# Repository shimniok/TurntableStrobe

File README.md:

# TurntableStrobe

Check your turntable's speed with TurntableStrobe, a highly accurate, tiny, low-cost, handheld turntable strobe. Or retrofit your turntable with the permanent-mount version.

With a crystal rated ±0.003% accuracy at 25°C, it is far more accurate than a mains frequency strobe on most turntables.

For sale on [Tindie](https://www.tindie.com/products/bot_thoughts/pocket-turntable-strobe/)

[Documentation](https://github.com/shimniok/TurntableStrobe/tree/master/documentation/)

## Features

* Crystal rated at ±0.003% accuracy at 25°C
* Use these free strobe discs: 60HzStrobeDisc.pdf or 50HzStrobeDisc.pdf
* Tiny CR1225 battery, included
* 1" long (not including the LED) x 3/4" wide
* Tactile on switch
* Handheld or Permanent mount

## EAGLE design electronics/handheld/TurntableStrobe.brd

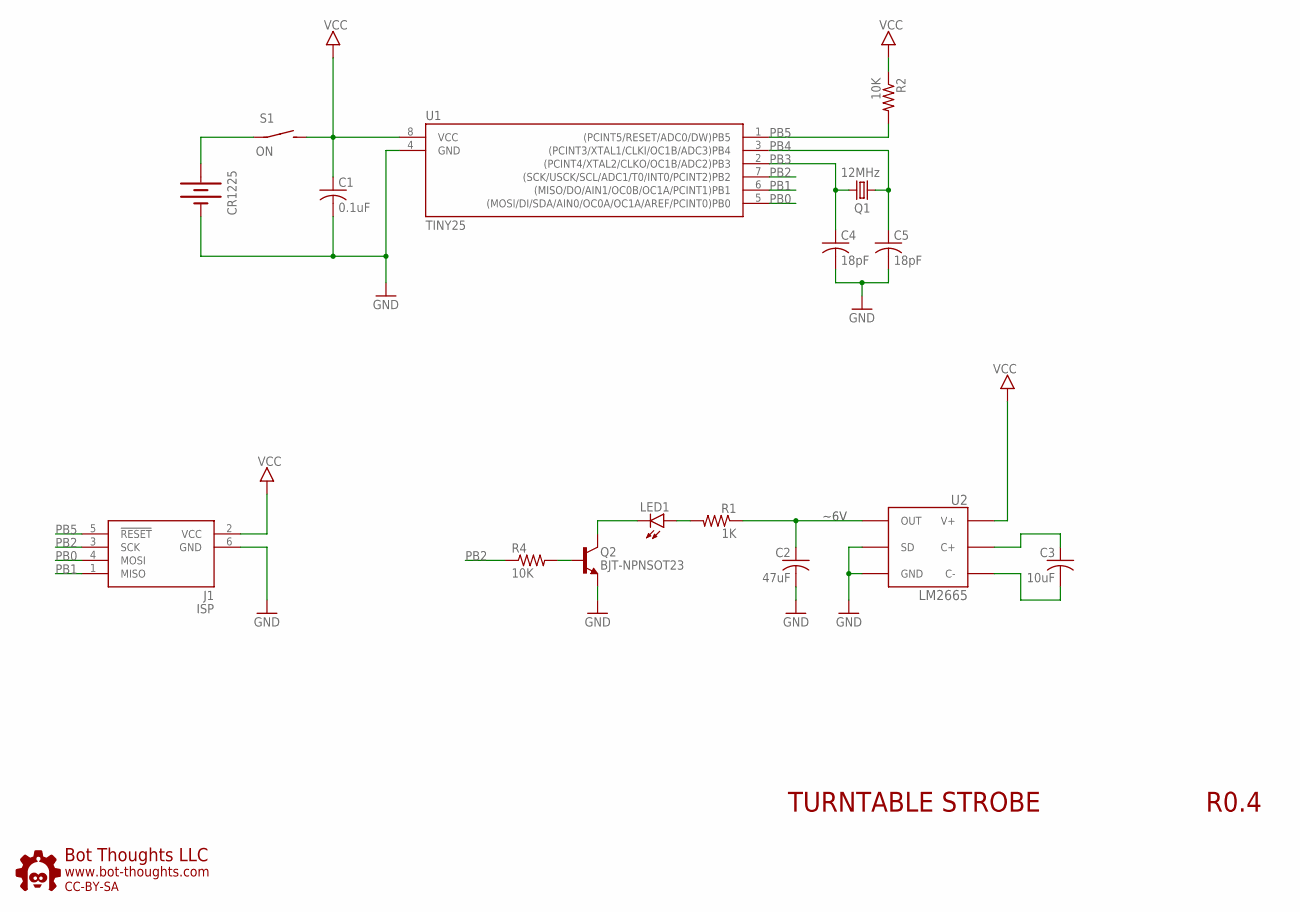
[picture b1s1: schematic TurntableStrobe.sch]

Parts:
C1: 0.1uF; C0603
C2: 47uF; C0603
C3: 10uF; C0603
C4, C5: 18pF; C0603
CR1225: BATTERY12PTH; BATTCON_12MM_PTH
J1: ISP; 2X3_TP
LED1: LED5MMRA
Q1: 12MHz; NDK_2PAD_5X3
Q2: BJT-NPNSOT23; SOT-23
R1: 1K; R0603
R2, R4: 10K; R0603
S1: ON; 6MMTACTILE_RECT
U1: TINY25; SOIC8N
U2: LM2665; SOT23-6
U$5: BTLOGO-LOGO-SM; BTLOGOS

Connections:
GND: C1.2, C2.2, C4.2, C5.2, CR1225.GND (-), J1.6 (GND), Q2.2 (E), U1.4 (GND), U2.2 (GND), U2.4 (SD)
unnamed: Q2.3 (B), R4.2
unnamed: C3.1, U2.6 (C+)
unnamed: LED1.A, R1.2
unnamed: C3.2, U2.3 (C-)
unnamed: LED1.C, Q2.1 (C)
PB0: J1.4 (MOSI), U1.5 ((MOSI/DI/SDA/AIN0/OC0A/OC1A/AREF/PCINT0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)
PB1: J1.1 (MISO), U1.6 ((MISO/DO/AIN1/OC0B/OC1A/PCINT1)PB1)
PB2: J1.3 (SCK), R4.1, U1.7 ((SCK/USCK/SCL/ADC1/T0/INT0/PCINT2)PB2)
PB3: C4.1, Q1.P$2 (2), U1.2 ((PCINT4/XTAL2/CLKO/OC1B/ADC2)PB3)
PB4: C5.1, Q1.P$1 (1), U1.3 ((PCINT3/XTAL1/CLKI/OC1B/ADC3)PB4)
PB5: J1.5 (!RESET), R2.2, U1.1 ((PCINT5/RESET/ADC0/DW)PB5)
VBAT: CR1225.VCC@1 (+), S1.P$1
VCC: C1.1, J1.2 (VCC), R2.1, S1.P$2 (S), U1.8 (VCC), U2.1 (V+)
VHI: C2.1, R1.1, U2.5 (OUT)

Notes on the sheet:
~6V
TURNTABLE STROBE
R0.4

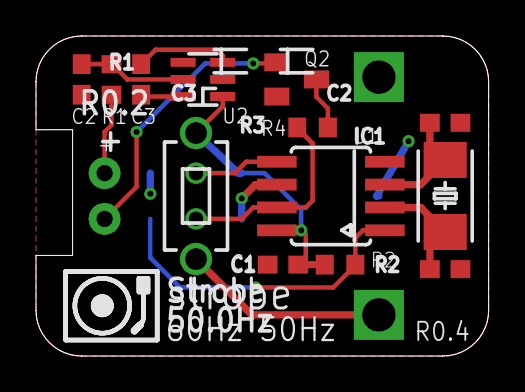
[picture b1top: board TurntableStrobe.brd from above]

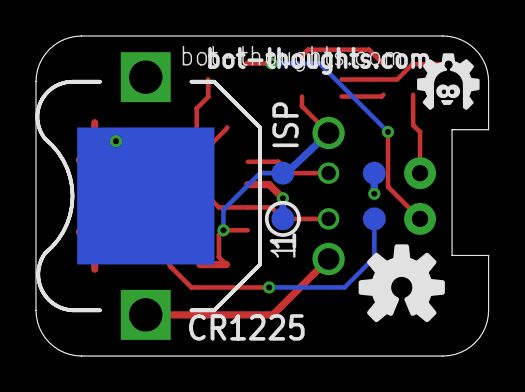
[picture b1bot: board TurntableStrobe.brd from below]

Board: 2 copper layers, 25.1 x 17.8 mm, 17 parts (3 on the bottom side), 15 nets.

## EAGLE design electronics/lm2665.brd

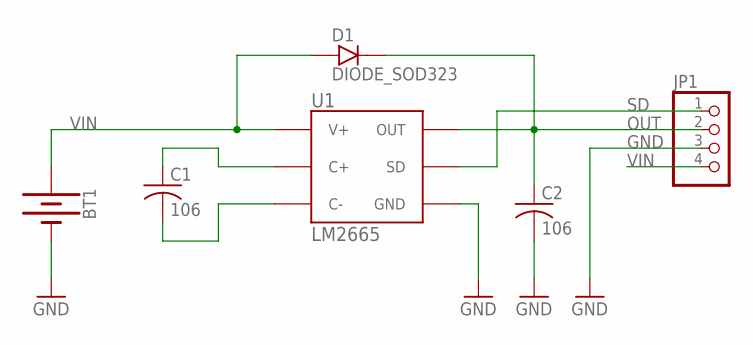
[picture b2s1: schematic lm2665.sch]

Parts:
BT1: BATTERY-12MM_PTH; BATTCON_12MM_PTH
C1, C2: 106; 1206
D1: DIODE_SOD323; SOD-323
JP1: PINHD-1X04_2.54-S; 1X04-S
U1: LM2665; SOT23-6

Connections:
GND: BT1.GND (-), C2.2 (-), JP1.3, U1.2 (GND)
unnamed: C1.1 (+), U1.6 (C+)
unnamed: C1.2 (-), U1.3 (C-)
OUT: C2.1 (+), D1.C, JP1.2, U1.5 (OUT)
SD: JP1.1, U1.4 (SD)
VIN: BT1.VCC@1 (+), D1.A, JP1.4, U1.1 (V+)

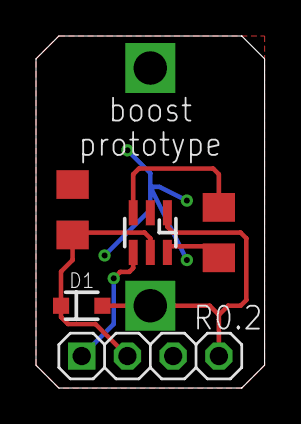
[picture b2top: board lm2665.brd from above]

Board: 2 copper layers, 12.7 x 19.6 mm, 6 parts (1 on the bottom side), 6 nets.

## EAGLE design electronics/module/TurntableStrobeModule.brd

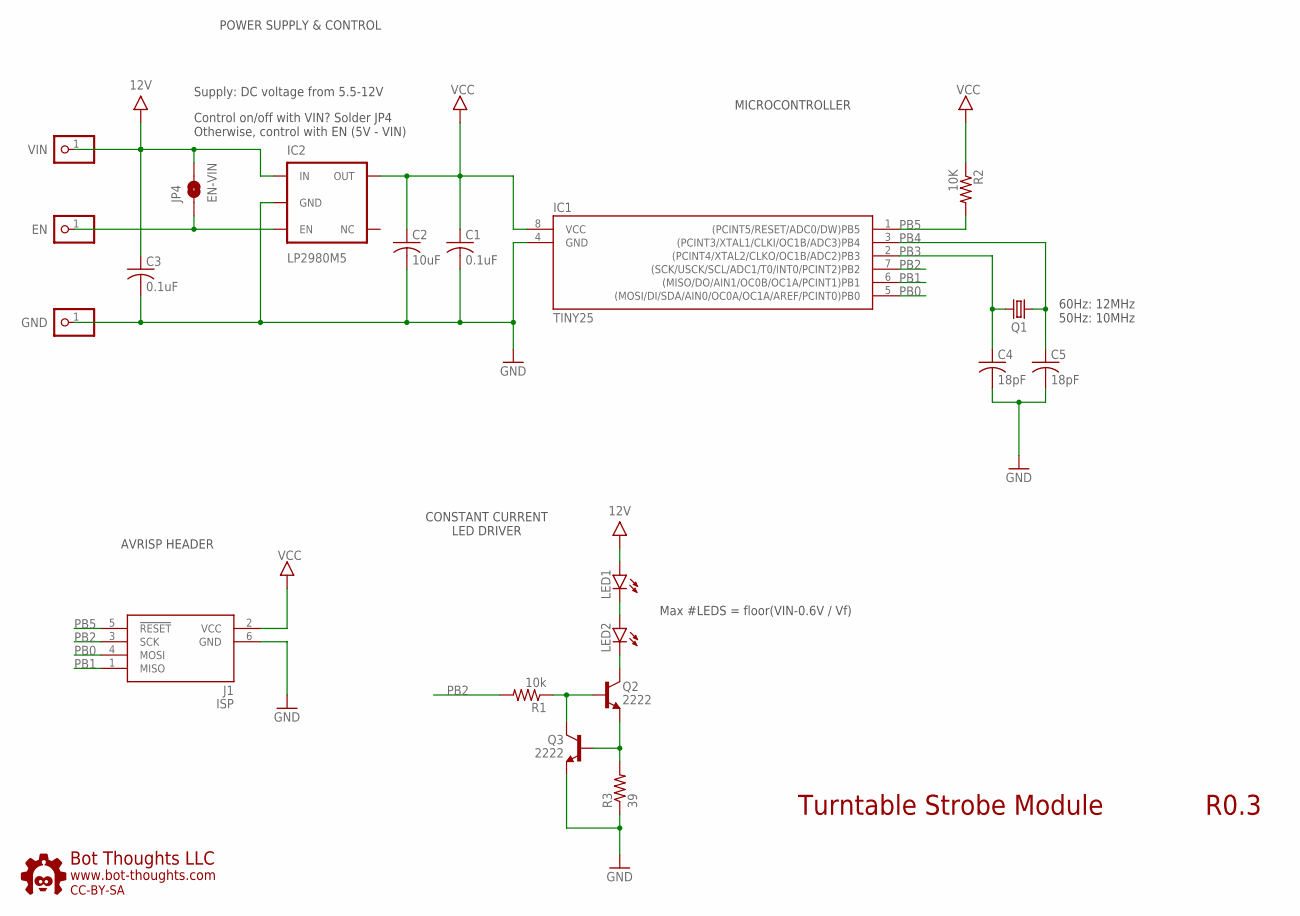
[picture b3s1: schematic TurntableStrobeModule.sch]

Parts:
C1, C3: 0.1uF; 0603
C2: 10uF; 1206
C4, C5: 18pF; 0603
IC1: TINY25; SOIC8N
IC2: LP2980M5; SOT23-5
J1: ISP; CON6P2R
JP1: EN; 1X01-S
JP2: VIN; 1X01-S
JP3: GND; 1X01-S
JP4: EN-VIN; SMT-JUMPER_2_NO_SILK
LED1, LED2: LED5MMRA
Q1: CRYSTALNDK5X3; NDK_2PAD_5X3
Q2, Q3: 2222; SOT-23
R1: 10k; 0603
R2: 10K; 0603
R3: 39; 0603
U$6: BTLOGO-LOGO-MD; BTLOGOM

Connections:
9V: C3.1 (+), IC2.1 (IN), JP2.1, JP4.2, LED1.A
GND: C1.2 (-), C2.2 (-), C3.2 (-), C4.2 (-), C5.2 (-), IC1.4 (GND), IC2.2 (GND), J1.6 (GND), JP3.1, Q3.2 (E), R3.1
unnamed: Q2.3 (B), Q3.1 (C), R1.1
unnamed: LED1.C, LED2.A
unnamed: LED2.C, Q2.1 (C)
unnamed: Q2.2 (E), Q3.3 (B), R3.2
unnamed: IC2.3 (EN), JP1.1, JP4.1
PB0: IC1.5 ((MOSI/DI/SDA/AIN0/OC0A/OC1A/AREF/PCINT0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), J1.4 (MOSI)
PB1: IC1.6 ((MISO/DO/AIN1/OC0B/OC1A/PCINT1)PB1), J1.1 (MISO)
PB2: IC1.7 ((SCK/USCK/SCL/ADC1/T0/INT0/PCINT2)PB2), J1.3 (SCK), R1.2
PB3: C4.1 (+), IC1.2 ((PCINT4/XTAL2/CLKO/OC1B/ADC2)PB3), Q1.P$2 (2)
PB4: C5.1 (+), IC1.3 ((PCINT3/XTAL1/CLKI/OC1B/ADC3)PB4), Q1.P$1 (1)
PB5: IC1.1 ((PCINT5/RESET/ADC0/DW)PB5), J1.5 (!RESET), R2.2
VCC: C1.1 (+), C2.1 (+), IC1.8 (VCC), IC2.5 (OUT), J1.2 (VCC), R2.1

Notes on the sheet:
Turntable Strobe Module
R0.3
60Hz: 12MHz 50Hz: 10MHz
Control on/off with VIN? Solder JP4 Otherwise, control with EN (5V - VIN)
Supply: DC voltage from 5.5-12V
Max #LEDS = floor(VIN-0.6V / Vf)
CONSTANT CURRENT LED DRIVER
AVRISP HEADER
POWER SUPPLY & CONTROL
MICROCONTROLLER

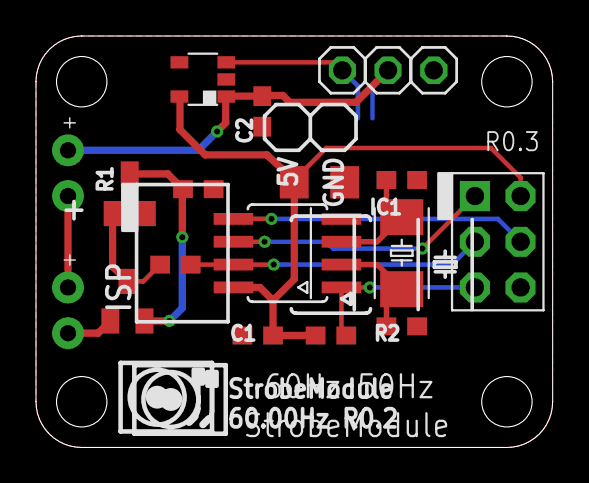
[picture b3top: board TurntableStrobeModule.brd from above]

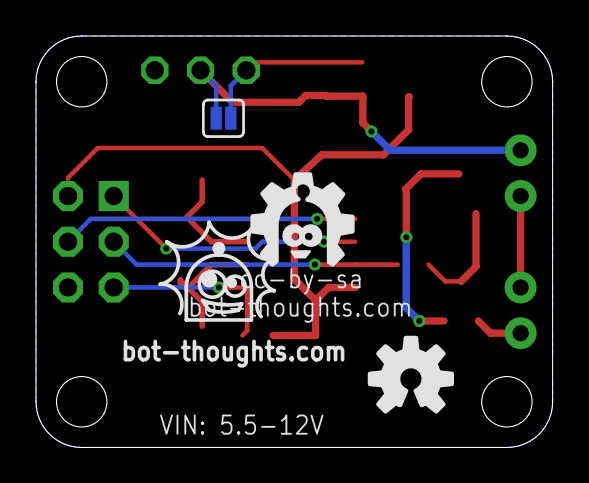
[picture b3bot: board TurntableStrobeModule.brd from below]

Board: 2 copper layers, 28.7 x 22.9 mm, 21 parts (2 on the bottom side), 14 nets.

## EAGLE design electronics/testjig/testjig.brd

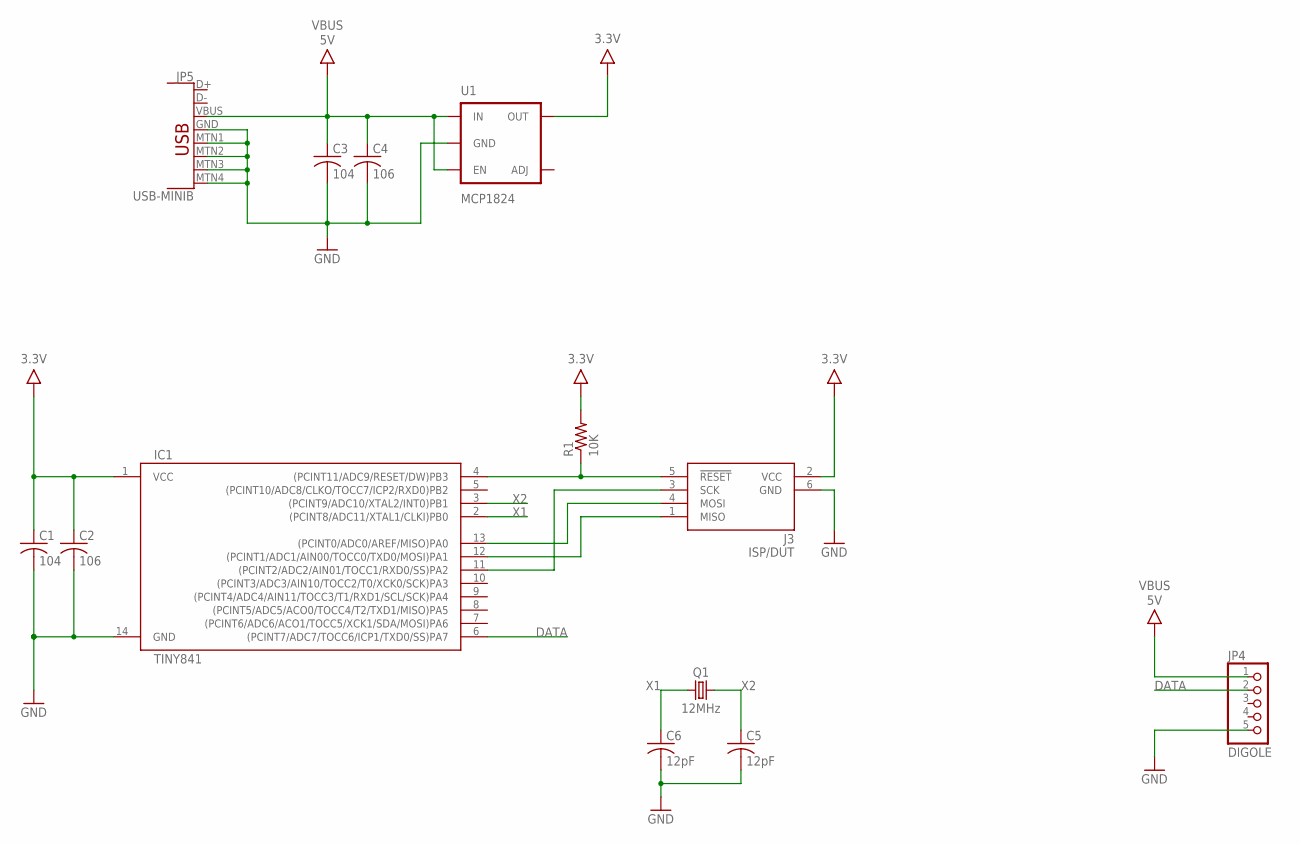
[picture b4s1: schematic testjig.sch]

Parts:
C1, C3: 104; 0603
C2, C4: 106; 0603
C5, C6: 12pF; 0603
IC1: TINY841; SOIC14N
J3: ISP/DUT; CON6P2R
JP4: DIGOLE; 1X05-S
JP5: USB-MINIB
Q1: 12MHz; NDK_2PAD_5X3
R1: 10K; 0603
U1: MCP1824; SOT23-5

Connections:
3.3V: C1.1 (+), C2.1 (+), IC1.1 (VCC), J3.2 (VCC), R1.2, U1.5 (OUT)
DATA: IC1.6 ((PCINT7/ADC7/TOCC6/ICP1/TXD0/SS)PA7), JP4.2
GND: C1.2 (-), C2.2 (-), C3.2 (-), C4.2 (-), C5.2 (-), C6.2 (-), IC1.14 (GND), J3.6 (GND), JP4.5, JP5.GND, JP5.MTN1 (SHIELD1), JP5.MTN2 (SHIELD2), JP5.MTN3 (SHIELD3), JP5.MTN4 (SHIELD4), U1.2 (GND)
PA0: IC1.13 ((PCINT0/ADC0/AREF/MISO)PA0), J3.4 (MOSI)
PA1: IC1.12 ((PCINT1/ADC1/AIN00/TOCC0/TXD0/MOSI)PA1), J3.1 (MISO)
PA2: IC1.11 ((PCINT2/ADC2/AIN01/TOCC1/RXD0/SS)PA2), J3.3 (SCK)
RESET: IC1.4 ((PCINT11/ADC9/RESET/DW)PB3), J3.5 (!RESET), R1.1
VBUS: C3.1 (+), C4.1 (+), JP4.1, JP5.VBUS, U1.1 (IN), U1.3 (EN)
X1: C6.1 (+), IC1.2 ((PCINT8/ADC11/XTAL1/CLKI)PB0), Q1.P$1 (1)
X2: C5.1 (+), IC1.3 ((PCINT9/ADC10/XTAL2/INT0)PB1), Q1.P$2 (2)

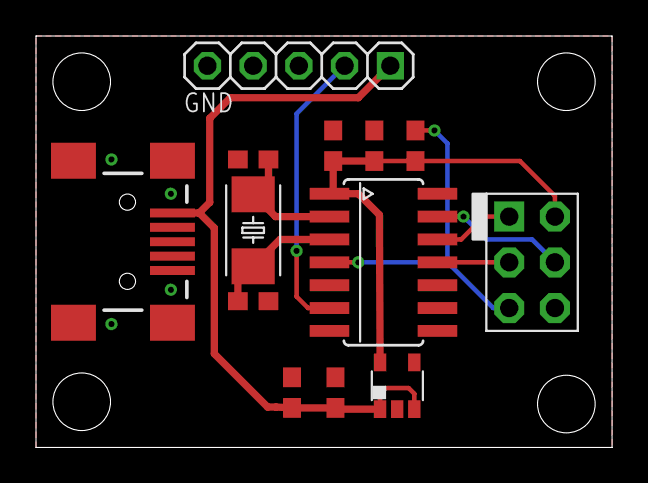
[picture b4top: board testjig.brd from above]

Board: 2 copper layers, 32.0 x 22.9 mm, 13 parts (0 on the bottom side), 10 nets.

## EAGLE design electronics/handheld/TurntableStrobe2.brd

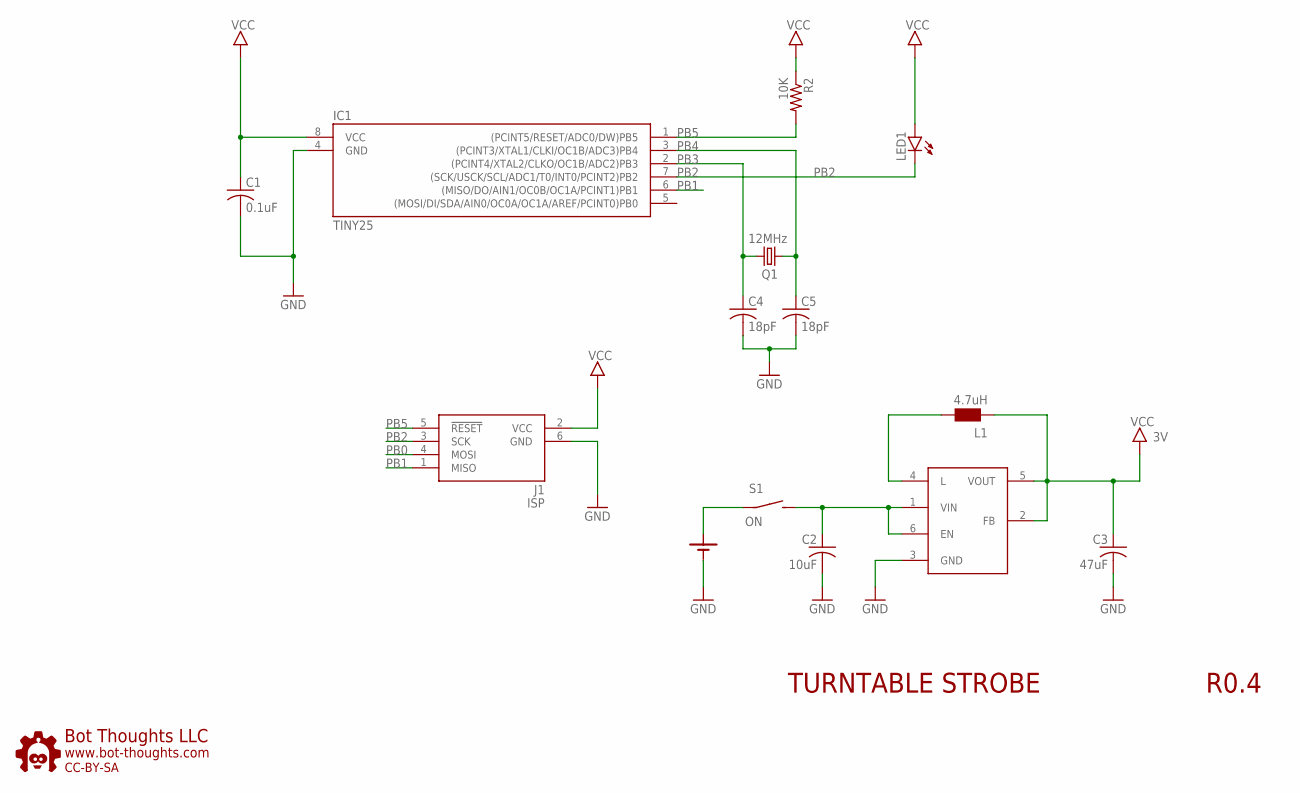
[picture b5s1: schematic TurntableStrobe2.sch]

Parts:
C1: 0.1uF; C0603
C2: 10uF; C0603
C3: 47uF; 1206
C4, C5: 18pF; C0603
CR1225: LR44_PTH; LR44
IC1: TINY25; SOIC8N
J1: ISP; 2X3_TP
L1: 4.7uH; 0805
LED1: LED5MMRA
Q1: 12MHz; NDK_2PAD_5X3
R2: 10K; R0603
S1: ON; 6MMTACTILE_RECT
U1: TLV61224; SC70-6
U$5: BTLOGO-LOGO-MD; BTLOGOM

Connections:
GND: C1.2, C2.2, C3.2 (-), C4.2, C5.2, CR1225.GND (-), IC1.4 (GND), J1.6 (GND), U1.3 (GND)
unnamed: L1.2, U1.4 (L)
PB0: J1.4 (MOSI)
PB1: IC1.6 ((MISO/DO/AIN1/OC0B/OC1A/PCINT1)PB1), J1.1 (MISO)
PB2: IC1.7 ((SCK/USCK/SCL/ADC1/T0/INT0/PCINT2)PB2), J1.3 (SCK), LED1.C
PB3: C4.1, IC1.2 ((PCINT4/XTAL2/CLKO/OC1B/ADC2)PB3), Q1.P$2 (2)
PB4: C5.1, IC1.3 ((PCINT3/XTAL1/CLKI/OC1B/ADC3)PB4), Q1.P$1 (1)
PB5: IC1.1 ((PCINT5/RESET/ADC0/DW)PB5), J1.5 (!RESET), R2.2
VBAT: CR1225.+1 (+), CR1225.+2 (+), S1.P$1
VCC: C1.1, C3.1 (+), IC1.8 (VCC), J1.2 (VCC), L1.1, LED1.A, R2.1, U1.2 (FB), U1.5 (VOUT)
VIN: C2.1, S1.P$2 (S), U1.1 (VIN), U1.6 (EN)

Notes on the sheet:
TURNTABLE STROBE
R0.4

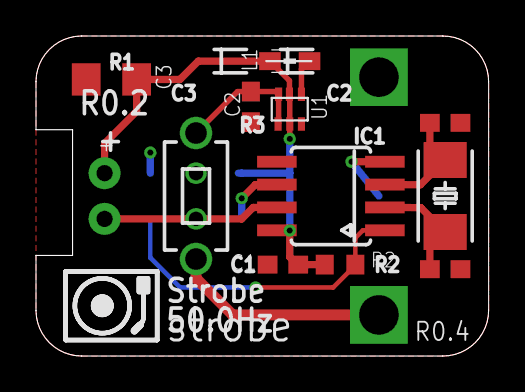
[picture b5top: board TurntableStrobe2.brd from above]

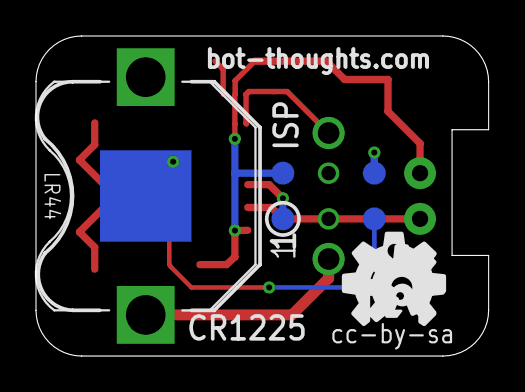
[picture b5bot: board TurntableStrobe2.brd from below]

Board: 2 copper layers, 25.1 x 17.8 mm, 15 parts (3 on the bottom side), 10 nets.

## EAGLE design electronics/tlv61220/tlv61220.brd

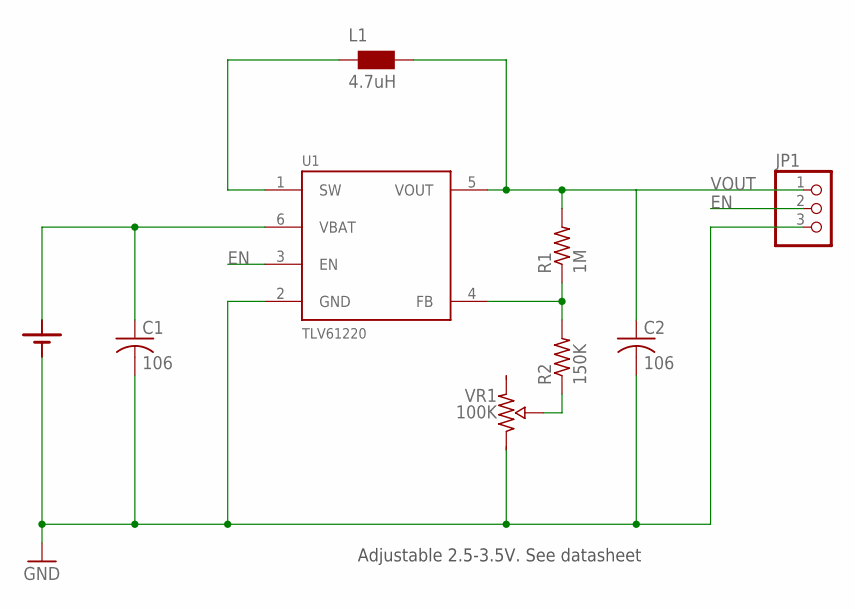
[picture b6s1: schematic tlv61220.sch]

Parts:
C1, C2: 106; 1206
JP1: PINHD-1X03_2.54-S; 1X03-S
L1: 4.7uH; WE-KI_0805_B
R1: 1M; 0603
R2: 150K; 0603
U1: TLV61220; SOT23-6
U$1: LR44_PTH; LR44
VR1: 100K; POT_0.2X0.25

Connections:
EN: JP1.2, U1.3 (EN)
GND: C1.2 (-), C2.2 (-), JP1.3, U1.2 (GND), U$1.GND (-), VR1.A
unnamed: C1.1 (+), U1.6 (VBAT), U$1.+1 (+), U$1.+2 (+)
unnamed: R1.1, R2.2, U1.4 (FB)
unnamed: R2.1, VR1.W (WIPER)
SW: L1.2 (1), U1.1 (SW)
VOUT: C2.1 (+), JP1.1, L1.1 (2), R1.2, U1.5 (VOUT)

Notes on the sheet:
Adjustable 2.5-3.5V. See datasheet

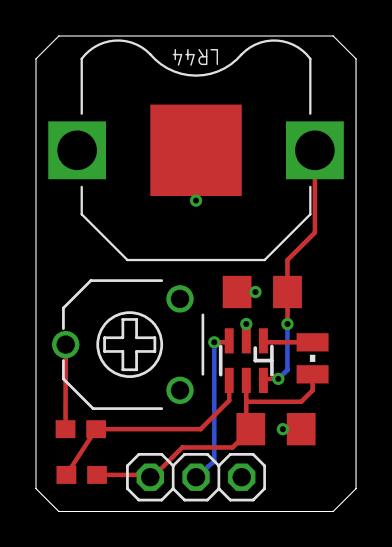
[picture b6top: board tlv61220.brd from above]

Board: 2 copper layers, 17.8 x 26.4 mm, 9 parts (0 on the bottom side), 7 nets.

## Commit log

2015-03-17 updated gitignore
2015-03-17 updated with different numbers to support 12mhz(60hz) 10mhz(50hz) operation with identical binaries
2015-03-17 updated makefile with slower bitclock to fix programming problems
2015-03-19 Reverted to original code. Fixed original makefile for much slower bitclock so I can flash these with LED installed
2015-03-20 Reverted to original, then hardcoded period into code so we can use 10mhz/12mhz xtals to determine frequency, tweaked isr to have count reset to 0 separately before main if-else
2015-03-20 updated TimingCalcs
2015-06-18 added safe operating area spreadsheet calcs/info
2015-06-19 Consolidated all calcs into single spreadsheet, added significant detail about safe operating area.
2015-07-02 Lowered frequency via CKDIV8, changed frequency to 120Hz/100Hz, moved charge pump toggle to ISR, added documentation, created function for led on/off
2015-11-10 slowed bitrate for programming; combined fuses and programming into single command line
2015-11-10 Placed F_CPU in config.h
2015-11-10 mods to design calculations spreadsheet
2016-01-22 updated readme with features, links to documentation and tindie listing
2016-01-22 initial user guide
2016-01-23 fixed documentation link
2016-01-25 added pictures, included pictures in user guide, plus minor rewording / revision
2016-01-25 removed svg
2016-01-25 fixed documentation links
2016-03-07 added solder jumper for easier reprogramming. Minor silk tweaks. New logo.
2016-03-07 updated to allow zips
2016-03-07 removed extraneous files
2016-03-07 subdirectory for ttstrobe module
2016-03-07 subdir for handheld and module
2016-03-08 Lastest version as ordered
2017-05-01 Created test jig
2017-05-17 zip of gerbers
2017-05-17 added queue module for capture
2017-05-17 test jig capture based on t841
2019-06-05 TLV61220 initial test run
2019-06-05 updates to design calculations
2019-06-05 lr44, boost ttstrobe, initial.
2019-06-05 Test jig initial(?)
2019-06-05 added regulator onboard, changed some packages
2019-06-05 initial testjig firmware
2019-06-05 enclosure, initial version
2019-06-05 added/enabled usbasp programmer
2019-06-05 added bulk program script
2019-06-12 initial working version of enclosure
2020-01-16 Timing parameters added to makefile & source
2021-09-14 separate build dirs, added usage
2021-09-16 diode array replaces discrete
2021-09-19 improvements to makefile
2021-09-19 improvements to bulk program script
2021-09-19 updates to design calcs spreadsheet
2021-10-20 Prototype LM2665 charge pump
2021-10-21 index on proto3: 4796ad3 Prototype LM2665 charge pump
2021-10-21 replace charge pump with ic
2021-10-21 updated sch with todo items, fixed brd silk
2021-10-21 fixed error in makefile
2021-10-21 updated silkscreen
2021-10-21 update code to use transistor (active high)
2021-10-21 restored lm2665 changes to brd/sch
2021-10-22 updated documentation, code for bjt driven led
2021-10-22 updated supply caps

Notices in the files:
electronics/handheld/TurntableStrobe2.brd:
cc-by-sa
parts and their libraries:
SparkFun: Licensing: CC v3.0 Share-Alike You are welcome to use this library for commercial purposes.
SparkFun-Retired: Licensing:Creative Commons ShareAlike 4.0 International - https://creativecommons.org/licenses/by-sa/4.0
wuerth-elektronik: Copyright: Würth Elektronik eiSos
